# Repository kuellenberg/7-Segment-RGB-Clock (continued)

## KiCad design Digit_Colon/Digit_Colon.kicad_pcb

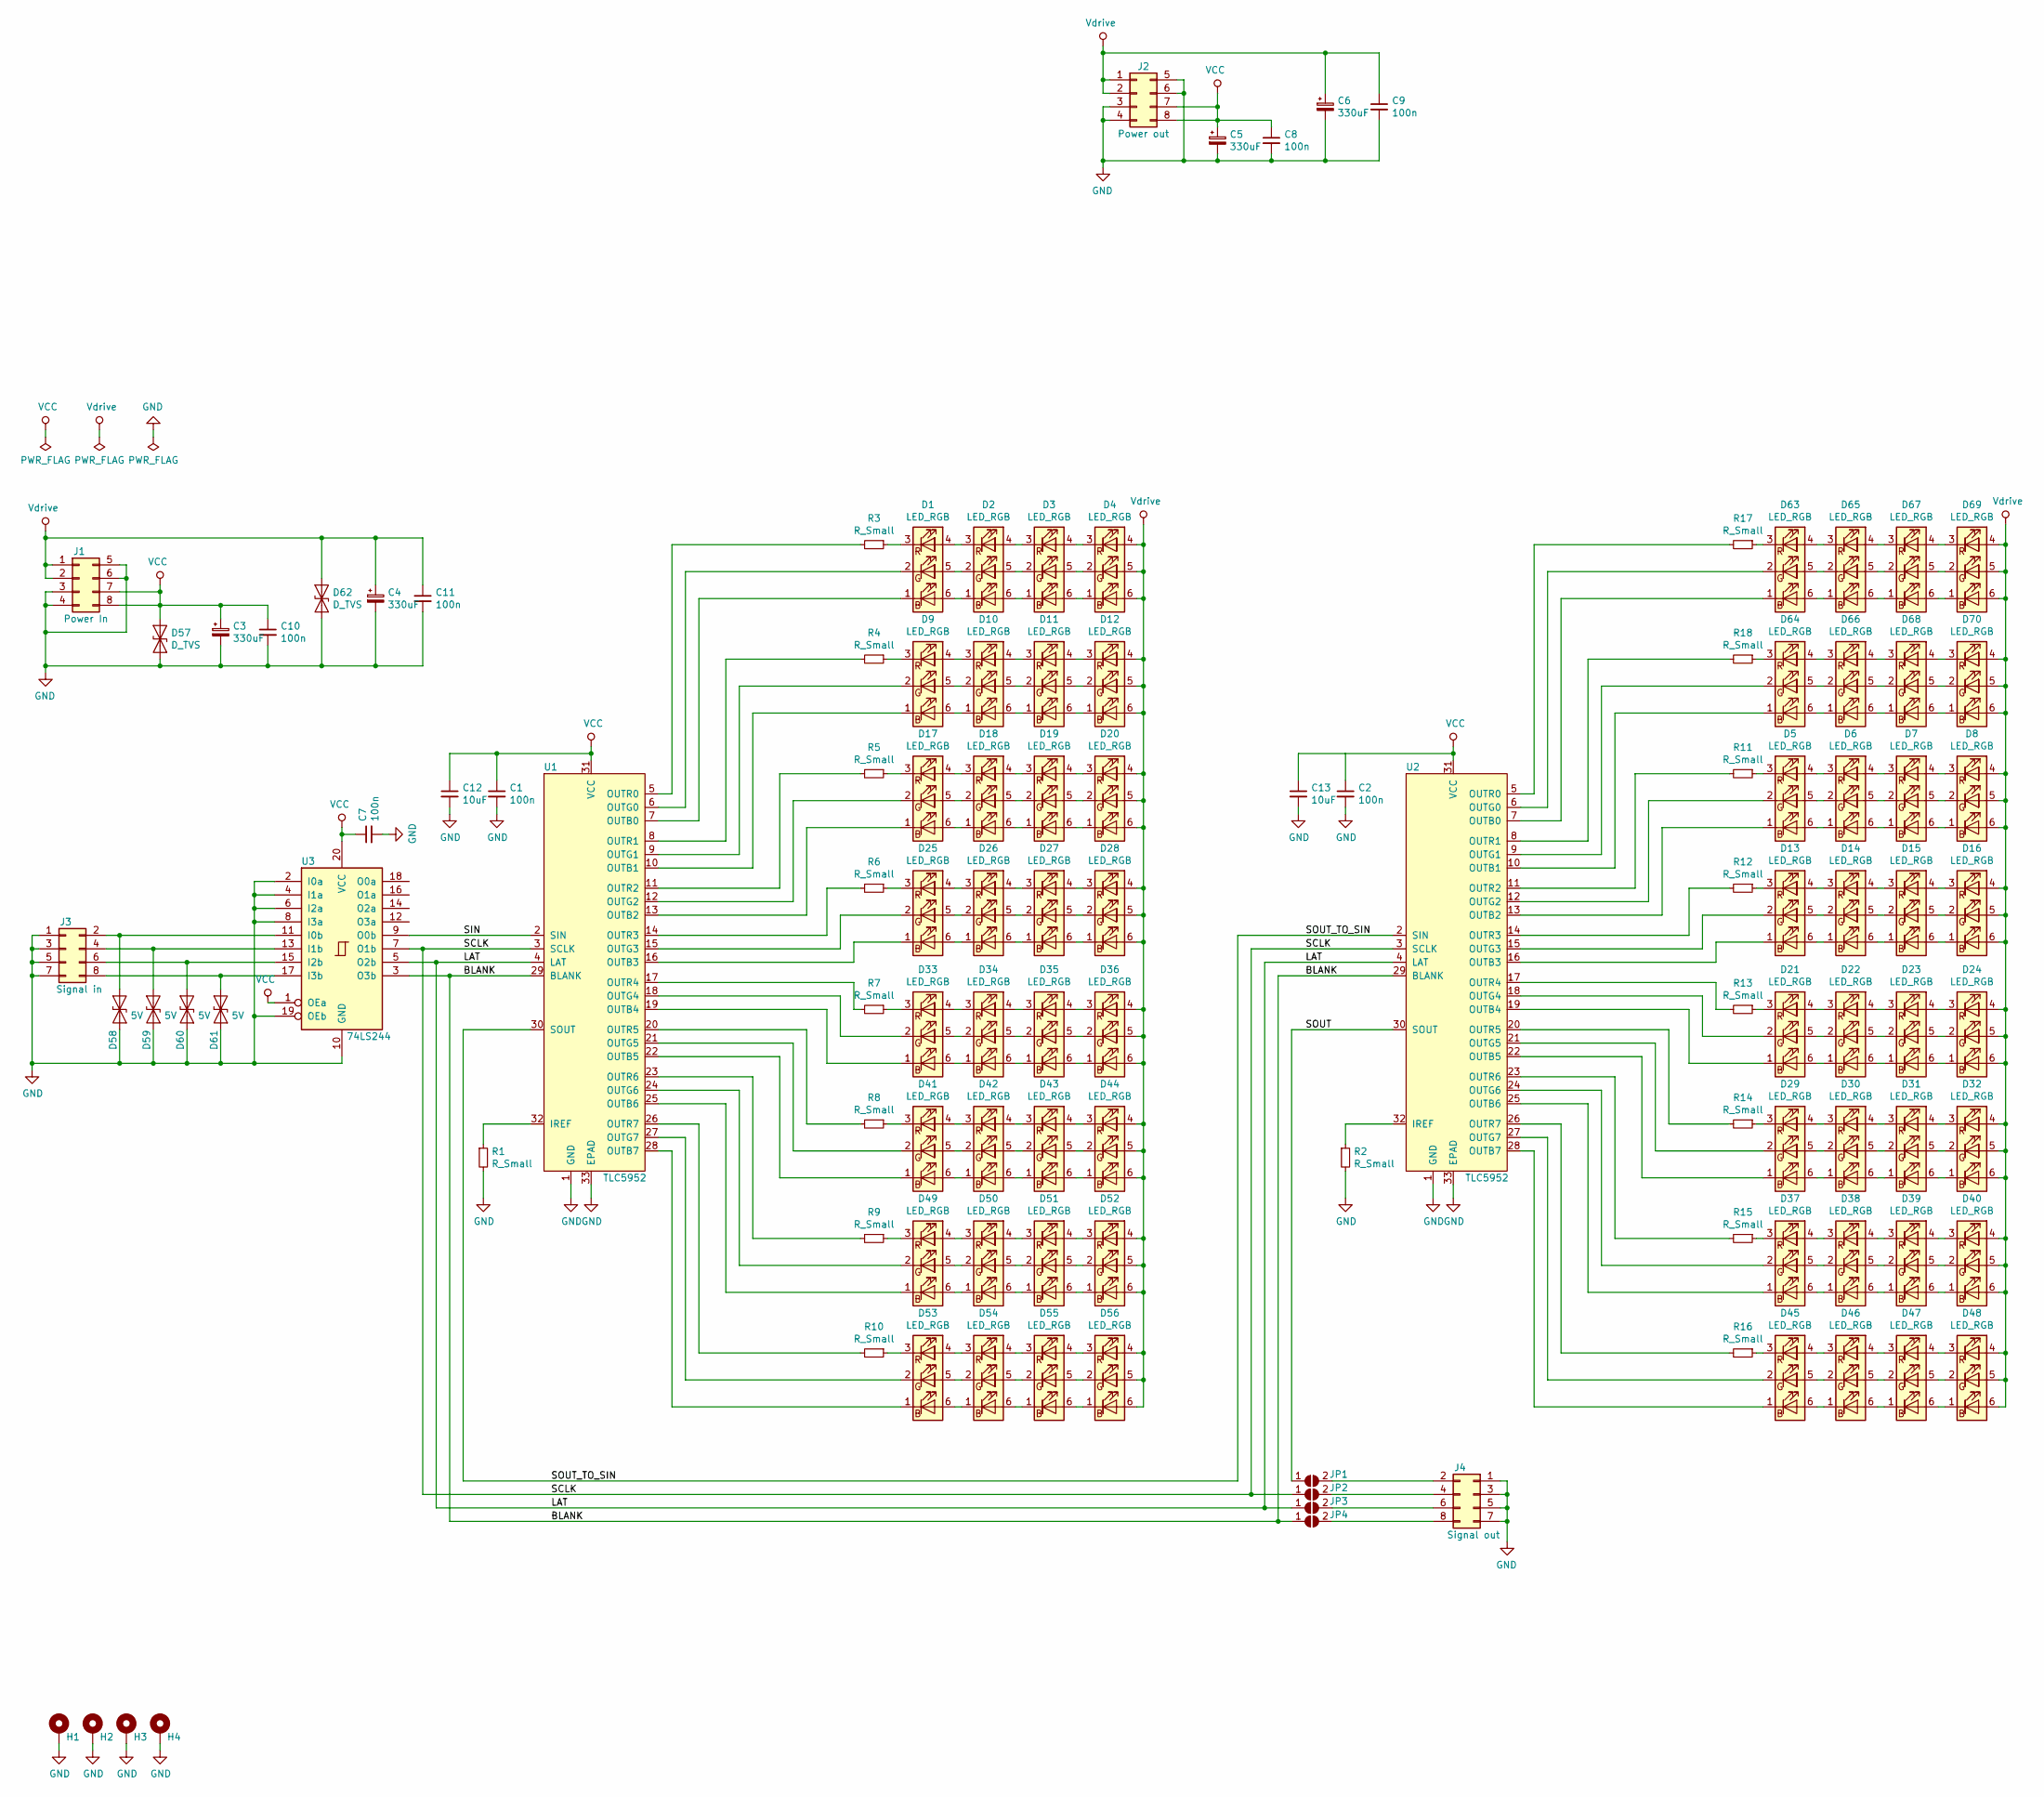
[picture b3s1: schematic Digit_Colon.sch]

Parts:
C1, C2, C7, C8, C9, C10, C11: 100n; C_0805_2012Metric
C3, C4, C5, C6: 330uF; C_Elec_8x10.2
C12, C13: 10uF; C_0805_2012Metric
D1, D2, D3, D4, D5, D6, D7, D8, D9, D10, D11, D12, D13, D14, D15, D16, D17, D18, D19, D20, D21, D22, D23, D24, D25, D26, D27, D28, D29, D30, D31, D32, D33, D34, D35, D36, D37, D38, D39, D40, D41, D42, D43, D44, D45, D46, D47, D48, D49, D50, D51, D52, D53, D54, D55, D56, D63, D64, D65, D66, D67, D68, D69, D70: LED_RGB; LED_RGB_5050-6
D57, D62: D_TVS; D_SMA
D58, D59, D60, D61: 5V; D_SOD-323
H1, H2, H3, H4: MountingHole_Pad; MountingHole_3.2mm_M3_Pad_Via
J1: Power In; HARWIN_M20-8890845
J2: Power out; HARWIN_M20-7910842R
J3: Signal in; HARWIN_M20-7910842R
J4: Signal out; HARWIN_M20-8890845
JP1, JP2, JP3, JP4: SolderJumper_2_Open; SolderJumper-2_P1.3mm_Open_TrianglePad1.0x1.5mm
R1, R2, R3, R4, R5, R6, R7, R8, R9, R10, R11, R12, R13, R14, R15, R16, R17, R18: R_Small; R_0805_2012Metric
U1, U2: TLC5952; HTSSOP-32-1EP_6.1x11mm_P0.65mm_EP5.2x11mm_Mask4.11x4.36mm_T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
U3: 74LS244; SO-20_12.8x7.5mm_P1.27mm

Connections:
+5VD: C1.1, C2.1, C3.1, C5.1, C7.1, C8.1, C10.1, C12.1, C13.1, D57.1 (A1), J1.7, J1.8, J2.7, J2.8, U1.31 (VCC), U2.31 (VCC), U3.1 (OEa), U3.20 (VCC)
+15V: C4.1, C6.1, C9.1, C11.1, D4.4 (RA), D4.5 (GA), D4.6 (BA), D8.4 (RA), D8.5 (GA), D8.6 (BA), D12.4 (RA), D12.5 (GA), D12.6 (BA), D16.4 (RA), D16.5 (GA), D16.6 (BA), D20.4 (RA), D20.5 (GA), D20.6 (BA), D24.4 (RA), D24.5 (GA), D24.6 (BA), D28.4 (RA), D28.5 (GA), D28.6 (BA), D32.4 (RA), D32.5 (GA), D32.6 (BA), D36.4 (RA), D36.5 (GA), D36.6 (BA), D40.4 (RA), D40.5 (GA), D40.6 (BA), D44.4 (RA), D44.5 (GA), D44.6 (BA), D48.4 (RA), D48.5 (GA), D48.6 (BA), D52.4 (RA), D52.5 (GA), D52.6 (BA), D56.4 (RA), D56.5 (GA), D56.6 (BA), D62.1 (A1), D69.4 (RA), D69.5 (GA), D69.6 (BA), D70.4 (RA), D70.5 (GA), D70.6 (BA), J1.1, J1.2, J2.1, J2.2
/BLANK: JP4.1 (A), U1.29 (BLANK), U2.29 (BLANK), U3.3 (O3b)
/LAT: JP3.1 (A), U1.4 (LAT), U2.4 (LAT), U3.5 (O2b)
/SCLK: JP2.1 (A), U1.3 (SCLK), U2.3 (SCLK), U3.7 (O1b)
/SIN: U1.2 (SIN), U3.9 (O0b)
/SOUT: JP1.1 (A), U2.30 (SOUT)
/SOUT_TO_SIN: U1.30 (SOUT), U2.2 (SIN)
GND: C1.2, C2.2, C3.2, C4.2, C5.2, C6.2, C7.2, C8.2, C9.2, C10.2, C11.2, C12.2, C13.2, D57.2 (A2), D58.2 (A2), D59.2 (A2), D60.2 (A2), D61.2 (A2), D62.2 (A2), H1.1, H2.1, H3.1, H4.1, J1.3, J1.4, J1.5, J1.6, J2.3, J2.4, J2.5, J2.6, J3.1, J3.3, J3.5, J3.7, J4.1, J4.3, J4.5, J4.7, R1.2, R2.2, U1.1 (GND), U1.33 (EPAD), U2.1 (GND), U2.33 (EPAD), U3.2 (I0a), U3.4 (I1a), U3.6 (I2a), U3.8 (I3a), U3.10 (GND), U3.19 (OEb)
unnamed: D1.1 (BK), U1.7 (OUTB0)
unnamed: D1.2 (GK), U1.6 (OUTG0)
unnamed: D1.3 (RK), R3.1
unnamed: D1.4 (RA), D2.3 (RK)
unnamed: D1.5 (GA), D2.2 (GK)
unnamed: D1.6 (BA), D2.1 (BK)
unnamed: D2.4 (RA), D3.3 (RK)
unnamed: D2.5 (GA), D3.2 (GK)
unnamed: D2.6 (BA), D3.1 (BK)
unnamed: D3.4 (RA), D4.3 (RK)
unnamed: D3.5 (GA), D4.2 (GK)
unnamed: D3.6 (BA), D4.1 (BK)
unnamed: D5.1 (BK), U2.13 (OUTB2)
unnamed: D5.2 (GK), U2.12 (OUTG2)
unnamed: D5.3 (RK), R11.1
unnamed: D5.4 (RA), D6.3 (RK)
unnamed: D5.5 (GA), D6.2 (GK)
unnamed: D5.6 (BA), D6.1 (BK)
unnamed: D6.4 (RA), D7.3 (RK)
unnamed: D6.5 (GA), D7.2 (GK)
unnamed: D6.6 (BA), D7.1 (BK)
unnamed: D7.4 (RA), D8.3 (RK)
unnamed: D7.5 (GA), D8.2 (GK)
unnamed: D7.6 (BA), D8.1 (BK)
unnamed: D9.1 (BK), U1.10 (OUTB1)
unnamed: D9.2 (GK), U1.9 (OUTG1)
unnamed: D9.3 (RK), R4.1
unnamed: D9.6 (BA), D10.1 (BK)
unnamed: D9.5 (GA), D10.2 (GK)
unnamed: D9.4 (RA), D10.3 (RK)
unnamed: D10.4 (RA), D11.3 (RK)
unnamed: D10.5 (GA), D11.2 (GK)
unnamed: D10.6 (BA), D11.1 (BK)
unnamed: D11.4 (RA), D12.3 (RK)
unnamed: D11.5 (GA), D12.2 (GK)
unnamed: D11.6 (BA), D12.1 (BK)
unnamed: D13.1 (BK), U2.16 (OUTB3)
unnamed: D13.2 (GK), U2.15 (OUTG3)
unnamed: D13.3 (RK), R12.1
unnamed: D13.4 (RA), D14.3 (RK)
unnamed: D13.5 (GA), D14.2 (GK)
unnamed: D13.6 (BA), D14.1 (BK)
unnamed: D14.4 (RA), D15.3 (RK)
unnamed: D14.5 (GA), D15.2 (GK)
unnamed: D14.6 (BA), D15.1 (BK)
unnamed: D15.4 (RA), D16.3 (RK)
unnamed: D15.5 (GA), D16.2 (GK)
unnamed: D15.6 (BA), D16.1 (BK)
unnamed: D17.1 (BK), U1.13 (OUTB2)
unnamed: D17.2 (GK), U1.12 (OUTG2)
unnamed: D17.3 (RK), R5.1
unnamed: D17.4 (RA), D18.3 (RK)
unnamed: D17.5 (GA), D18.2 (GK)
unnamed: D17.6 (BA), D18.1 (BK)
unnamed: D18.4 (RA), D19.3 (RK)
unnamed: D18.5 (GA), D19.2 (GK)
unnamed: D18.6 (BA), D19.1 (BK)
unnamed: D19.4 (RA), D20.3 (RK)
unnamed: D19.5 (GA), D20.2 (GK)
unnamed: D19.6 (BA), D20.1 (BK)
unnamed: D21.1 (BK), U2.19 (OUTB4)
unnamed: D21.2 (GK), U2.18 (OUTG4)
unnamed: D21.3 (RK), R13.1
unnamed: D21.4 (RA), D22.3 (RK)
unnamed: D21.5 (GA), D22.2 (GK)
unnamed: D21.6 (BA), D22.1 (BK)
unnamed: D22.4 (RA), D23.3 (RK)
unnamed: D22.5 (GA), D23.2 (GK)
unnamed: D22.6 (BA), D23.1 (BK)
unnamed: D23.4 (RA), D24.3 (RK)
unnamed: D23.5 (GA), D24.2 (GK)
unnamed: D23.6 (BA), D24.1 (BK)
unnamed: D25.1 (BK), U1.16 (OUTB3)
unnamed: D25.2 (GK), U1.15 (OUTG3)
unnamed: D25.3 (RK), R6.1
unnamed: D25.4 (RA), D26.3 (RK)
unnamed: D25.5 (GA), D26.2 (GK)
unnamed: D25.6 (BA), D26.1 (BK)
unnamed: D26.4 (RA), D27.3 (RK)
unnamed: D26.5 (GA), D27.2 (GK)
unnamed: D26.6 (BA), D27.1 (BK)
unnamed: D27.4 (RA), D28.3 (RK)
unnamed: D27.5 (GA), D28.2 (GK)
unnamed: D27.6 (BA), D28.1 (BK)
unnamed: D29.1 (BK), U2.22 (OUTB5)
unnamed: D29.2 (GK), U2.21 (OUTG5)
unnamed: D29.3 (RK), R14.1
unnamed: D29.4 (RA), D30.3 (RK)
unnamed: D29.5 (GA), D30.2 (GK)
unnamed: D29.6 (BA), D30.1 (BK)
unnamed: D30.4 (RA), D31.3 (RK)
unnamed: D30.5 (GA), D31.2 (GK)
unnamed: D30.6 (BA), D31.1 (BK)
unnamed: D31.4 (RA), D32.3 (RK)
unnamed: D31.5 (GA), D32.2 (GK)
unnamed: D31.6 (BA), D32.1 (BK)
unnamed: D33.1 (BK), U1.19 (OUTB4)
unnamed: D33.2 (GK), U1.18 (OUTG4)
unnamed: D33.3 (RK), R7.1
unnamed: D33.4 (RA), D34.3 (RK)
unnamed: D33.5 (GA), D34.2 (GK)
unnamed: D33.6 (BA), D34.1 (BK)
unnamed: D34.4 (RA), D35.3 (RK)
unnamed: D34.5 (GA), D35.2 (GK)
unnamed: D34.6 (BA), D35.1 (BK)
unnamed: D35.4 (RA), D36.3 (RK)
unnamed: D35.5 (GA), D36.2 (GK)
unnamed: D35.6 (BA), D36.1 (BK)
unnamed: D37.1 (BK), U2.25 (OUTB6)
unnamed: D37.2 (GK), U2.24 (OUTG6)
unnamed: D37.3 (RK), R15.1
unnamed: D37.4 (RA), D38.3 (RK)
unnamed: D37.5 (GA), D38.2 (GK)
unnamed: D37.6 (BA), D38.1 (BK)
unnamed: D38.4 (RA), D39.3 (RK)
unnamed: D38.5 (GA), D39.2 (GK)
unnamed: D38.6 (BA), D39.1 (BK)
unnamed: D39.4 (RA), D40.3 (RK)
unnamed: D39.5 (GA), D40.2 (GK)
unnamed: D39.6 (BA), D40.1 (BK)
unnamed: D41.1 (BK), U1.22 (OUTB5)
unnamed: D41.2 (GK), U1.21 (OUTG5)
unnamed: D41.3 (RK), R8.1
unnamed: D41.4 (RA), D42.3 (RK)
unnamed: D41.5 (GA), D42.2 (GK)
unnamed: D41.6 (BA), D42.1 (BK)
unnamed: D42.4 (RA), D43.3 (RK)
unnamed: D42.5 (GA), D43.2 (GK)
unnamed: D42.6 (BA), D43.1 (BK)
unnamed: D43.4 (RA), D44.3 (RK)
unnamed: D43.5 (GA), D44.2 (GK)
unnamed: D43.6 (BA), D44.1 (BK)
unnamed: D45.1 (BK), U2.28 (OUTB7)
unnamed: D45.2 (GK), U2.27 (OUTG7)
unnamed: D45.3 (RK), R16.1
unnamed: D45.4 (RA), D46.3 (RK)
unnamed: D45.5 (GA), D46.2 (GK)
unnamed: D45.6 (BA), D46.1 (BK)
unnamed: D46.4 (RA), D47.3 (RK)
unnamed: D46.5 (GA), D47.2 (GK)
unnamed: D46.6 (BA), D47.1 (BK)
unnamed: D47.4 (RA), D48.3 (RK)
unnamed: D47.5 (GA), D48.2 (GK)
unnamed: D47.6 (BA), D48.1 (BK)
unnamed: D49.1 (BK), U1.25 (OUTB6)
unnamed: D49.2 (GK), U1.24 (OUTG6)
unnamed: D49.3 (RK), R9.1
unnamed: D49.4 (RA), D50.3 (RK)
unnamed: D49.5 (GA), D50.2 (GK)
unnamed: D49.6 (BA), D50.1 (BK)
unnamed: D50.4 (RA), D51.3 (RK)
unnamed: D50.5 (GA), D51.2 (GK)
unnamed: D50.6 (BA), D51.1 (BK)
unnamed: D51.4 (RA), D52.3 (RK)
unnamed: D51.5 (GA), D52.2 (GK)
unnamed: D51.6 (BA), D52.1 (BK)
unnamed: D53.1 (BK), U1.28 (OUTB7)
unnamed: D53.2 (GK), U1.27 (OUTG7)
unnamed: D53.3 (RK), R10.1
unnamed: D53.4 (RA), D54.3 (RK)
unnamed: D53.5 (GA), D54.2 (GK)
unnamed: D53.6 (BA), D54.1 (BK)
unnamed: D54.4 (RA), D55.3 (RK)
unnamed: D54.5 (GA), D55.2 (GK)
unnamed: D54.6 (BA), D55.1 (BK)
unnamed: D55.4 (RA), D56.3 (RK)
unnamed: D55.5 (GA), D56.2 (GK)
unnamed: D55.6 (BA), D56.1 (BK)
unnamed: D58.1 (A1), J3.2, U3.11 (I0b)
unnamed: D59.1 (A1), J3.4, U3.13 (I1b)
unnamed: D60.1 (A1), J3.6, U3.15 (I2b)
unnamed: D61.1 (A1), J3.8, U3.17 (I3b)
unnamed: D63.1 (BK), U2.7 (OUTB0)
unnamed: D63.2 (GK), U2.6 (OUTG0)
unnamed: D63.3 (RK), R17.1
unnamed: D63.4 (RA), D65.3 (RK)
unnamed: D63.5 (GA), D65.2 (GK)
unnamed: D63.6 (BA), D65.1 (BK)
unnamed: D64.1 (BK), U2.10 (OUTB1)
unnamed: D64.2 (GK), U2.9 (OUTG1)
unnamed: D64.3 (RK), R18.1
unnamed: D64.4 (RA), D66.3 (RK)
unnamed: D64.5 (GA), D66.2 (GK)
unnamed: D64.6 (BA), D66.1 (BK)
unnamed: D65.4 (RA), D67.3 (RK)
unnamed: D65.5 (GA), D67.2 (GK)
unnamed: D65.6 (BA), D67.1 (BK)
unnamed: D66.4 (RA), D68.3 (RK)
unnamed: D66.5 (GA), D68.2 (GK)
unnamed: D66.6 (BA), D68.1 (BK)
unnamed: D67.4 (RA), D69.3 (RK)
unnamed: D67.5 (GA), D69.2 (GK)
unnamed: D67.6 (BA), D69.1 (BK)
unnamed: D68.4 (RA), D70.3 (RK)
unnamed: D68.5 (GA), D70.2 (GK)
unnamed: D68.6 (BA), D70.1 (BK)
unnamed: J4.2, JP1.2 (B)
unnamed: J4.4, JP2.2 (B)
unnamed: J4.6, JP3.2 (B)
unnamed: J4.8, JP4.2 (B)
unnamed: R1.1, U1.32 (IREF)
unnamed: R2.1, U2.32 (IREF)
unnamed: R3.2, U1.5 (OUTR0)
unnamed: R4.2, U1.8 (OUTR1)
unnamed: R5.2, U1.11 (OUTR2)
unnamed: R6.2, U1.14 (OUTR3)
unnamed: R7.2, U1.17 (OUTR4)
unnamed: R8.2, U1.20 (OUTR5)
unnamed: R9.2, U1.23 (OUTR6)
unnamed: R10.2, U1.26 (OUTR7)
unnamed: R11.2, U2.11 (OUTR2)
unnamed: R12.2, U2.14 (OUTR3)
unnamed: R13.2, U2.17 (OUTR4)
unnamed: R14.2, U2.20 (OUTR5)
unnamed: R15.2, U2.23 (OUTR6)
unnamed: R16.2, U2.26 (OUTR7)
unnamed: R17.2, U2.5 (OUTR0)
unnamed: R18.2, U2.8 (OUTR1)

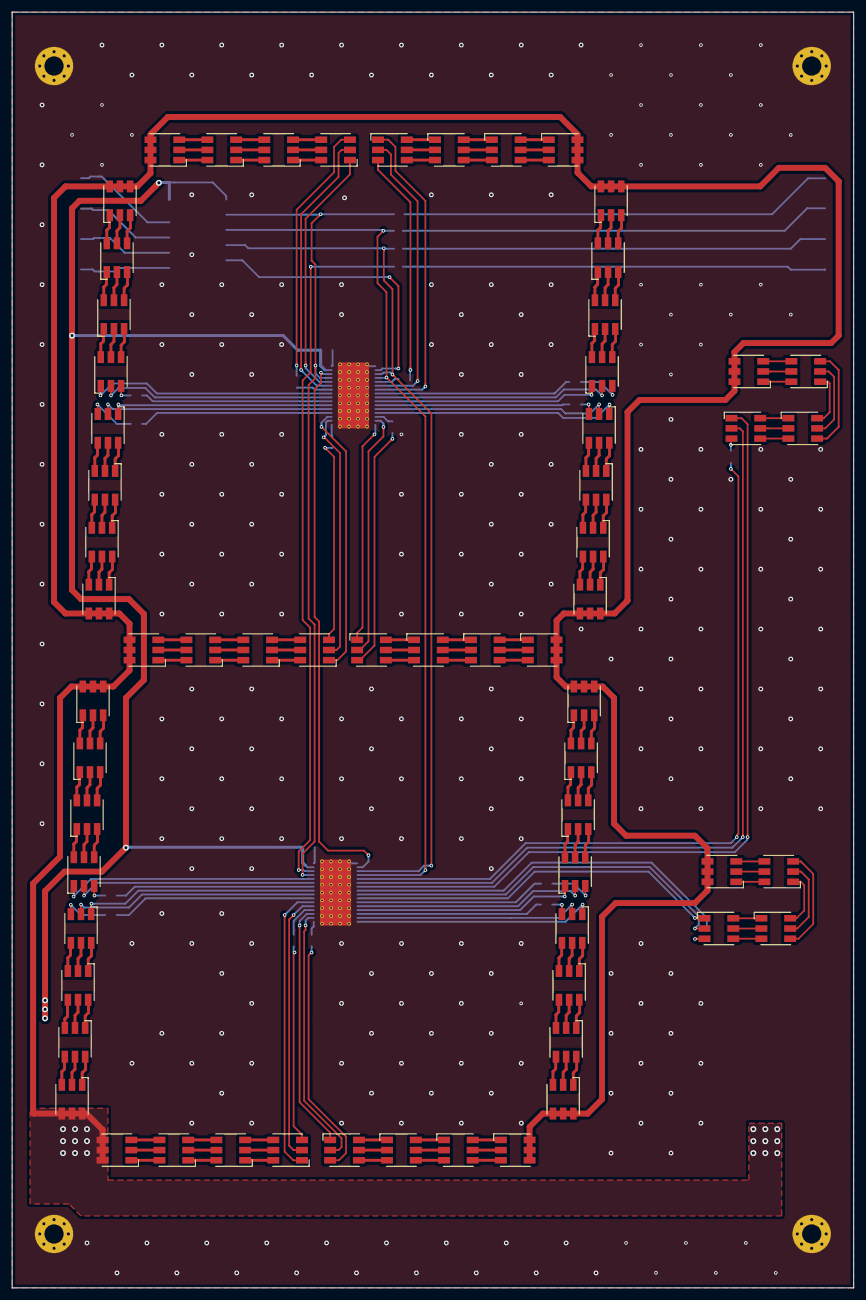
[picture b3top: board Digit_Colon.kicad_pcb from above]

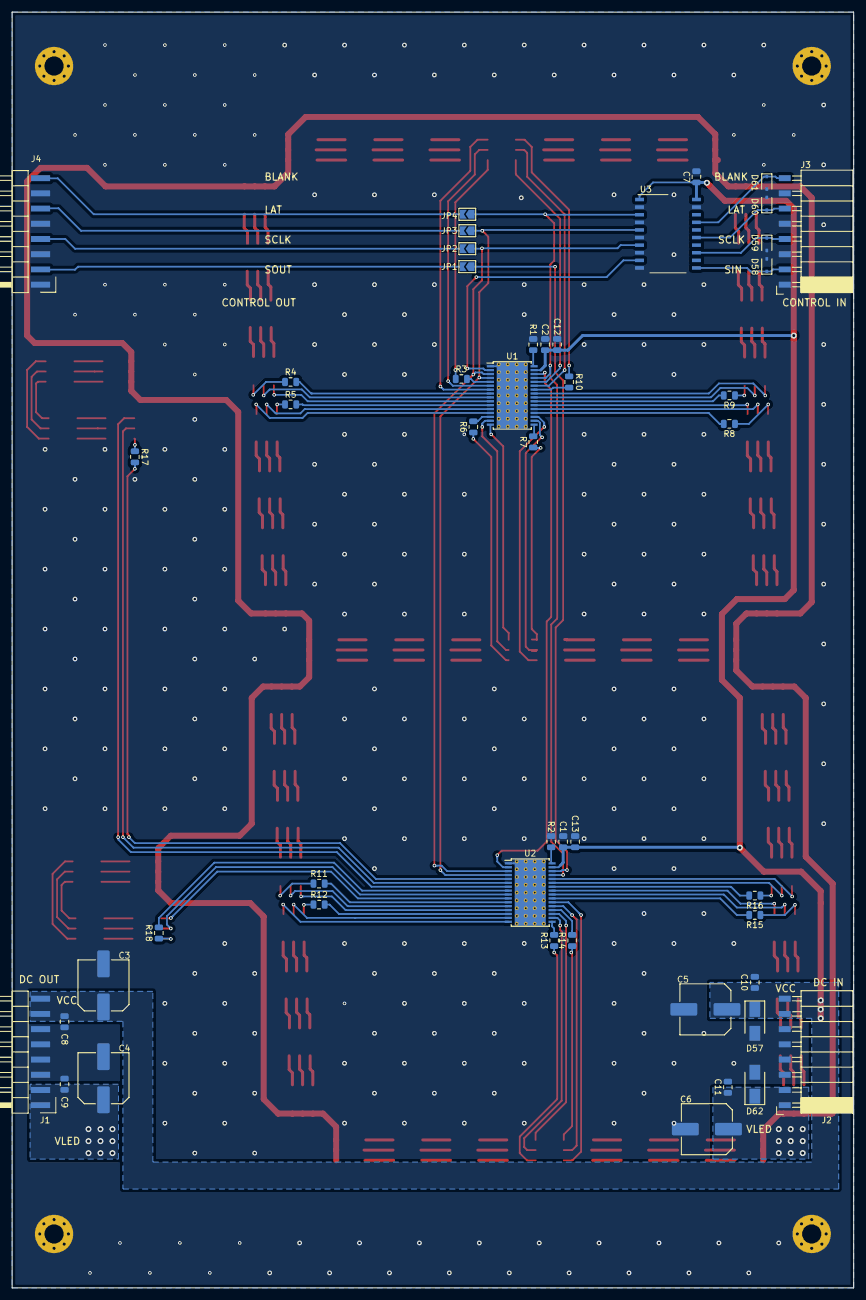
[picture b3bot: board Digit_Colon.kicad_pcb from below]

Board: 2 copper layers, 140.5 x 213.0 mm, 116 parts (48 on the bottom side), 227 nets.

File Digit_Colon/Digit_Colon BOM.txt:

Reference, Quantity, Value, Footprint, Datasheet, Mouser, Label
C1 C2 C7 C10 C11 C9 C8 ,7,"100n","Capacitor_SMD:C_0805_2012Metric","~","810-CGA3E2X7R1H104K ",""
C12 C13 ,2,"10uF","Capacitor_SMD:C_0805_2012Metric","~","81-GRM21BR71A106KA3K",""
C4 C3 C5 C6 ,4,"330uF","Capacitor_SMD:C_Elec_8x10.2","~","667-EEE-HA1E331UP ",""
D25 D26 D27 D28 D48 D47 D46 D45 D40 D39 D38 D37 D32 D31 D30 D24 D23 D22 D21 D16 D15 D14 D13 D8 D7 D6 D5 D29 D4 D3 D2 D1 D36 D35 D34 D33 D53 D54 D55 D56 D41 D42 D43 D44 D12 D11 D10 D9 D20 D19 D18 D17 D52 D51 D50 D49 D70 D68 D66 D64 D69 D67 D65 D63 ,64,"LED_RGB","LED_SMD:LED_RGB_5050-6","~"
D57 D62 ,2,"6V TVS","Diode_SMD:D_SMA","~","652-SMAJ6.0CA ",""
D60 D61 D59 D58 ,4,"5V TVS","Diode_SMD:D_SOD-323","~","576-AQ05C-01FTG ",""
J1 J4 ,2,"Conn_02x04_Odd_Even","ak:HARWIN_M20-8890845","~","855-M20-8890845","DC in"
J3 J2 ,2,"Conn_02x04_Odd_Even","ak:HARWIN_M20-7910842R","~","855-M20-7910842R","Signal in"
R1 R2 ,2,"TBD","Resistor_SMD:R_0805_2012Metric","~","71-CRCW08050000Z0EAC",""
R3 R4 R5 R6 R7 R8 R9 R10 R12 R13 R14 R15 R16 R11 R18 R17 ,16,"0R","Resistor_SMD:R_0805_2012Metric","~","603-RT0805DRE071K58L",""
U1 U2 ,2,"TLC5952","Package_SO:HTSSOP-32-1EP_6.1x11mm_P0.65mm_EP5.2x11mm_Mask4.11x4.36mm_ThermalVias","","595-TLC5952DAP",""
U3 ,1,"74LS244","Package_SO:SO-20_12.8x7.5mm_P1.27mm","http://www.ti.com/lit/gpn/sn74LS244","595-SN74LS244DWR",""

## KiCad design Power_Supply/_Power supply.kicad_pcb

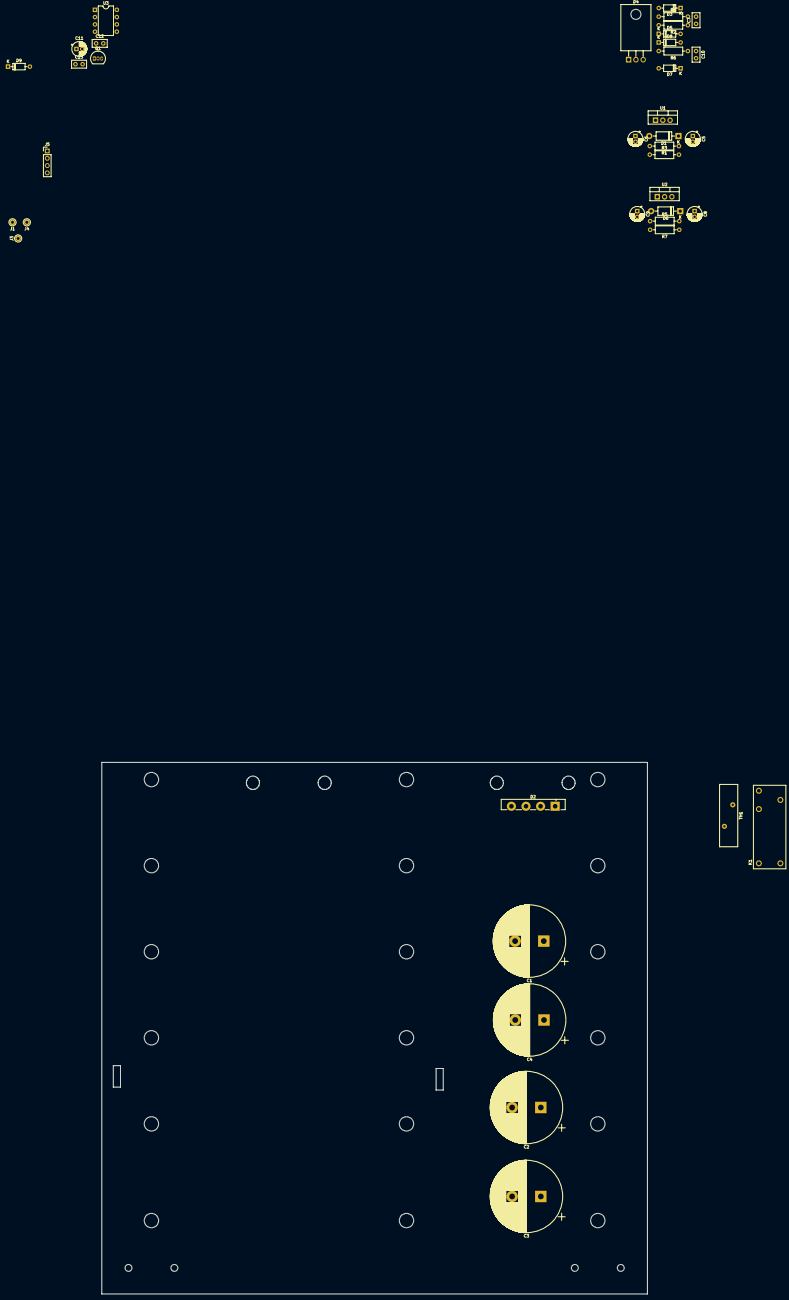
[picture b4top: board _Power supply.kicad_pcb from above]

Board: 2 copper layers, 190.2 x 185.3 mm, 39 parts (0 on the bottom side), 18 nets, no tracks yet.

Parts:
C1, C2, C3, C4: 4700uF; CP_Radial_D25.0mm_P10.00mm_SnapIn
C5, C6, C8, C9, C11: 10uF; CP_Radial_D5.0mm_P2.00mm
C7, C10, C12, C13: 100nF; C_Disc_D5.0mm_W2.5mm_P2.50mm
D1, D6: 1N5819; D_DO-41_SOD81_P10.16mm_Horizontal
D2: D_Bridge_+AA-; Diode_Bridge_Vishay_GBU
D3: 12V; D_DO-35_SOD27_P7.62mm_Horizontal
D4: Q_SCR_KAG; TO-220F-3_Horizontal_TabDown
D5, D8, D9: 1N4148; D_DO-35_SOD27_P7.62mm_Horizontal
D7: 5V; D_DO-35_SOD27_P7.62mm_Horizontal
J1, J3, J4: Conn_01x01; Pin_D1.0mm_L10.0mm
J5: Conn_01x04; PinHeader_1x04_P2.54mm_Vertical
K1: RY611012
Q1: BC548; TO-92_Inline
R1, R3: 100R; R_Axial_DIN0207_L6.3mm_D2.5mm_P10.16mm_Horizontal
R2, R6: 470R; R_Axial_DIN0207_L6.3mm_D2.5mm_P10.16mm_Horizontal
R4, R5: 100k; R_Axial_DIN0207_L6.3mm_D2.5mm_P10.16mm_Horizontal
R7: 10k; R_Axial_DIN0207_L6.3mm_D2.5mm_P10.16mm_Horizontal
TH1: 5R; RV_Disc_D21.5mm_W6.1mm_P7.5mm
U1: LM1084-12; TO-220-3_Vertical
U2: LM1084-5; TO-220-3_Vertical
U3: NE555P; DIP-8_W7.62mm

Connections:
+5V: C9.1, D6.2, D7.1, J5.2, U2.2
+12V: C6.1, C8.1, D1.2, D3.1, D6.1, D8.1, J5.1, K1.A1, R4.1, R5.1, U1.2, U2.3, U3.4, U3.8
GND: C1.2, C2.2, C3.2, C4.2, C5.2, C6.2, C7.2, C8.2, C9.2, C10.2, C11.2, C12.2, C13.2, D2.4, D4.1, J5.3, J5.4, Q1.3, R2.2, R6.2, U1.1, U2.1, U3.1
unnamed: C7.1, D5.2, R1.1
unnamed: C10.1, D9.2, R3.1
unnamed: C11.1, R4.2, U3.6, U3.7
unnamed: C12.1, U3.5
unnamed: C13.1, R5.2, U3.2
unnamed: D2.2, J1.1
unnamed: D2.3, K1.11, TH1.1
unnamed: D3.2, R1.2, R2.1
unnamed: D4.3, D5.1, D9.1
unnamed: D7.2, R3.2, R6.1
unnamed: D8.2, K1.A2, Q1.1
unnamed: J3.1, J4.1, K1.14, TH1.2
unnamed: Q1.2, R7.2
unnamed: R7.1, U3.3
VDC: C1.1, C2.1, C3.1, C4.1, C5.1, D1.1, D2.1, D4.2, U1.3

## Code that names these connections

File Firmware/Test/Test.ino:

int LAT=A3;
int BLANK=A2;
int SIN=A4;
int CLK=A5;

#define BLUE 1
#define RED 2
#define GREEN 4

const uint8_t SEGMAP[2][16] = {
  {0,0,0,0,0,0,0,0, 0,0,0,0,0,0,0,0},
  {1,1,1,1,1,1,1,1, 1,1,1,1,1,1,1,1}
};

const int redA[24] = {
  0,1,0,
  0,1,0,
  0,1,0,
  0,1,0,
  0,1,0,
  0,1,0,
  0,0,0,
  0,0,0
};
const int redB[24] = {
  0,1,0,
  0,1,0,
  0,1,0,
  0,1,0,
  0,1,0,
  0,1,0,
  0,1,0,
  0,1,0
};

const int green[24] = {
  1,0,0,
  1,0,0,
  1,0,0,
  1,0,0,
  1,0,0,
  1,0,0,
  1,0,0,
  1,0,0
};

const int blue[24] = {
  0,0,1,
  0,0,1,
  0,0,1,
  0,0,1,
  0,0,1,
  0,0,1,
  0,0,1,
  0,0,1
};

const int mixA[24] = {
  1,1,1,
  1,1,1,
  1,1,1,
  1,1,1,
  1,1,1,
  1,1,1,
  1,0,1,
  1,0,1
};
const int mixB[24] = {
  1,1,1,
  1,1,1,
  1,1,1,
  1,1,1,
  1,1,1,
  1,1,1,
  1,1,1,
  1,1,1
};
int cont[24] = {
  0,0,0,
  0,0,0,0,0,0,1,
  0,0,0,1,0,0,1,
  0,0,0,0,0,0,1,
};


void sendOnOffData(const uint8_t *data, uint8_t color) {
  for(int m=0; m<2; m++) {
    digitalWrite(SIN, LOW);
    digitalWrite(CLK, LOW);
    digitalWrite(CLK, HIGH);
    digitalWrite(CLK, LOW);
    for(int n=0; n<8; n++) {
      digitalWrite(SIN, (color & GREEN ? data[n*m] : 0));
      digitalWrite(CLK, HIGH);
      digitalWrite(CLK, LOW);
      digitalWrite(SIN, (color & RED ? data[n*m] : 0));
      digitalWrite(CLK, HIGH);
      digitalWrite(CLK, LOW);
      digitalWrite(SIN, (color & BLUE ? data[n*m] : 0));
      digitalWrite(CLK, HIGH);
      digitalWrite(CLK, LOW);
    }
  }
}

void latch() {
  digitalWrite(LAT, HIGH);
  digitalWrite(LAT, LOW);
}

void sendOnOff(const int *color) {
  digitalWrite(SIN, LOW);
  digitalWrite(CLK, LOW);
  digitalWrite(CLK, HIGH);
  digitalWrite(CLK, LOW);
  for(int n=0;n<24;n++) {
    digitalWrite(SIN, color[n]);
    digitalWrite(CLK, HIGH);
    digitalWrite(CLK, LOW);
  }
}

void sendCont() {
  digitalWrite(SIN, HIGH);
  digitalWrite(CLK, LOW);
  digitalWrite(CLK, HIGH);
  digitalWrite(CLK, LOW);
  for(int n=0;n<24;n++) {
    digitalWrite(SIN, cont[n]);
    digitalWrite(CLK, HIGH);
    digitalWrite(CLK, LOW);
  }
}

void setup() {
  // put your setup code here, to run once:
  pinMode(LAT, OUTPUT);
  pinMode(BLANK, OUTPUT);
  pinMode(SIN, OUTPUT);
  pinMode(CLK, OUTPUT);
  digitalWrite(LAT, LOW);

  Serial.begin(9600);
  
  digitalWrite(BLANK, HIGH); //all outp off
  /*
  sendOnOff(mixB);
  sendOnOff(mixB);
  sendOnOff(mixA);
  sendOnOff(mixB);
  
  sendOnOff(redB);
  sendOnOff(redB);
  sendOnOff(redA);
  sendOnOff(redB);
  */
  sendOnOffData(SEGMAP[1], BLUE|RED);
  sendOnOffData(SEGMAP[1], GREEN|RED);
  latch();
  
  sendCont();
  sendCont();
  sendCont();
  sendCont();
  latch();
  digitalWrite(BLANK, LOW); //all outp on
}

void loop() {
  /*
  digitalWrite(BLANK, HIGH); //all outp off
  sendOnOff(blue);
  sendOnOff(blue);
  sendOnOff(blue);
  sendOnOff(blue);
  latch();
  digitalWrite(BLANK, LOW); //all outp on
  delay(1000);
  
  digitalWrite(BLANK, HIGH); //all outp off
  sendOnOff(red);
  sendOnOff(red);
  sendOnOff(red);
  sendOnOff(red);
  latch();
  digitalWrite(BLANK, LOW); //all outp on
  delay(1000);
    
  digitalWrite(BLANK, HIGH); //all outp off
  sendOnOff(green);
  sendOnOff(green);
  sendOnOff(green);
  sendOnOff(green);
  latch();
  digitalWrite(BLANK, LOW); //all outp on
  delay(1000);
  */

  /*
  for(int n=0; n<=127; n++) {
    for(int m=0; m<24; m++) {
      cont[m] = 0;
    }
    Serial.print("n: ");
    Serial.println(n);
    for(int m=0; m<=7; m++) {
      cont[2 + 7-m] |= (n >> m) & 1;
      cont[10 + 7-m] |= (n >> m) & 1;
      cont[18 + 7-m] |= (n >> m) & 1;
    }
    for(int m=7; m>0; m--) {
      Serial.print(cont[10+m]);
      Serial.print(",");
    }
    Serial.println("");
    
    sendCont();
    sendCont();
    sendCont();
    sendCont();
    latch();
    delay(50);
  }
  Serial.println("----------------");
  */
}

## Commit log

2019-09-16 all change...
2019-09-18 Routing...
2019-09-19 Added line driver. Routing.
2019-09-20 Routing. Via stitching
2019-09-20 Moved PCB and origin.
2019-09-20 Square PCB
2019-09-20 Finished routing. Added text.
2019-09-21 Created digit with colon
2019-09-24 Added controller schematic
2019-09-25 Controller schematic...
2019-09-26 Controller...
2019-10-01 Ground vias digit+colon. Placement/routing controller
2019-10-02 Routing controller
2019-10-03 layout...
2019-10-04 Finished routing controller pcb.
2019-10-04 Created mounting bracket.
2019-10-04 Added rendered image.
2019-10-04 Minor changes. BOM
2019-10-04 Moved mounting holes. Moved stuff around on controller PCB.
2019-10-05 Modified controller layout. Fixed distance to board edge.
2019-10-29 minor layout change.
2019-11-27 BOM...
2019-12-11 Bug fixes: * Reset circuit - netlabel RESET -> /RESET - Reset button pulls high - FTDI DTR connected to reset line * Added pull-ups to RTC outputs * Moved status LED to PC1 TODO: * Add thermal relief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
2019-12-13 Added firmware
2019-12-13 Firmware testing
2019-12-14 Basic clock function implemented.
2020-03-07 Minor changes
2020-03-19 Replaced LDR with PD, changed USB connector.
2020-03-20 Layout updated
2020-03-25 Added Python control software
2020-03-26 Firmware...
2020-03-27 new rendered image
2020-03-28 shortened pcb by 1mm
2020-03-29 Software
2020-03-30 Software...
2020-03-30 WiFi-Controller
2020-05-12 Replaced 15V connector. Created BOM and Gerbers
2020-05-12 Added Mouser P/N
2020-05-13 BOM update
2020-06-01 Power Supply
2020-06-10 add BOM for RS Components
2020-07-15 PCB outline
2020-07-31 Assembly drawing
2020-08-10 BOM Controller
2021-01-03 about to merge
2022-01-26 ltspice
